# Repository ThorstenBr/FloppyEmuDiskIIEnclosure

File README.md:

# FloppyEmu Disk II Enclosure
This project contains OpenSCAD files, STL files, stickers and KiCad PCB to create a 3D-printed custom enclosure for the [Big Mess of Wires - FloppyEmu](https://www.bigmessowires.com/floppy-emu/) - an SD-card based disk drive emulator for the Apple II computer. The custom enclosure is a look-alike of the historic "Disk II" drive, Apple's first and hugely successful original disk drive for the Apple II, introduced in 1978.

As a bonus, this project also contains a housing for the Floppy Emu DB-19 plug adapter - a separate little 3D-print to protect the adapter (see "Bonus" section below).

## Credits
The idea for this 3D-printing project was triggered by similar ideas to create Disk II-shaped custom enclosures for the FloppyEmu in the [AppleFritter](http://www.applefritter.com) forum - a forum for vintage Apple computer fans. See [this discussion thread](https://www.applefritter.com/content/yet-another-floppyemu-enclosure-3d-printing-approach) for more.

## License
This project is released under the "Creative Commons Attribution 4.0 International Public License". See [LICENSE](/LICENSE).

The Apple logo is a registered trademark of Apple Computer Inc. Any images and photos which may show the Disk II-FloppyEmu enclosure with an Apple logo were only given as an example of how you could decorate your Disk II-FloppyEmu drive enclosure for your personal use, to match the retro look of your wonderful original Apple II computer. The 3D-printed Disk II FloppyEmu enclosure is not endorsed by Apple. This project does not grant you any rights or licenses to distribute any 3D-printed enclosures with an Apple logo.

## Design
The 3D design is done with OpenSCAD. All files are available in the [scad](/scad/) folder.

The OpenSCAD file provides an option to generate the enclosure in different sizes. The minimum scale to fit the FloppyEmu PCB is 0.6 (= 60% of the original Disk II enclosure size). Currently, this reduced size is the only variant which is tested. The photos of the enclosure also show this reduced variant. Larger sizes will still require some tweaking in the SCAD files. The full-sized variant will be supported in the future (wait for it...).
You can also choose whether to use one LED (status LED only), or two LEDs (status + power LED). One LED is the default.

You can also find a ready-to-use STL files in the [stl](/stl/) folder. These STL files apply to the tested variant (60% of the original, one LED).

## Button Panel
You will need a button panel, so you can control FloppyEmu from the front.
You can build the panel manually using a perfboard or order a printed circuit board (from JLCPCB etc).

The [pcb](/pcb/) folder contains all Gerber files required for a PCB order:

Alternatively, use a perfboard to solder the push buttons manually. It's only 4 buttons and a connector (and maybe the resistor for the status LED):

Schematics and the KiCad project for the PCB are also stored in [pcb](/pcb/) folder:

The button PCB is eventually screwed to the front panel (Note: the photo does not show the latest design. The PCB is now mounted with 4 screws, one in each corner - see newer PCB design above).

### Bill Of Materials

Here's what you need.

#### For the button panel:

- Manufactured PCB (i.e. upload the Gerber-Files to a PCB manufacturer, like JLCPCB). Alternatively use a [perfboard](https://en.wikipedia.org/wiki/Perfboard).
- 4x "micro switch push button 6x6x7mm" (ebay etc)
- 1x 3mm LED (red)
- 1x resistor (value depends on the type and intensity of your LED, usually 330 Ohm to 1KOhm)
- "2x5 box header" or, alternatively, "2x5 straight pin header"

The four push buttons are very common and easy to obtain. They are similar as the onboard buttons of FloppyEmu. Except the PCB design is made for a through-hole type push buttons (not SMD buttons as on FloppyEmu). Switches with a 7mm peg are required to properly mount the printed button caps. Check on ebay searching for "micro switch push button 6x6x7mm". Your favourite electronics supplier should also have them (Germany: reichelt.de, TASTER 9303, Kurzhubtaster 6x6mm, 7,0mm).

#### For the button panel and LCD connector:
- You can use simple breadboard wires ("jumper wires") to connect FloppyEmu to the button panel and LCD. They are cheap and also come with a ribbon cable. The LCD and the button panel both require 7 wires each (since 3 pins of the button panel's pin header are unused).

- Alternatively, use "header plugs" with matching ribbon cable (2x5 for the button panel, 2x8 for the LCD) - as shown in the build photos. This is a slightly more expensive and complex solution. 

## Wiring FloppyEmu
The FloppyEmu PCB does not provide convenient pins or solder pads to tap the button and LED status signals. However, it's still relatively easy to tap the required signals - as shown by these photos. The photos apply to the Revision C model of the BMOW FloppyEmu. For other revisions, better verify the wiring with a multimeter.

A single wire is enough for each push button is enough: all four push buttons, including the reset button, connect to common ground. The status LED, however, does not connect to ground: it's wired between the status output signal and +5V (via an appropriate resistor for the LED, of course). The only feasible place is to solder directly next to the LED. The status signal is on the right of the LED – as shown. Be careful when soldering – just touch the LED very briefly with the iron – otherwise the onboard LED will die.

You can wire the ground lead (common for all push buttons) and the 5V (for the status LED) to the unpopulated debug connector in the middle of the FloppyEmu PCB. I soldered these two on the PCB’s bottom side, so they are almost “invisible” once the PCB is installed.

I suggest you solder all wires to a 2x5 pin header (or boxed header), so you can use a neat ribbon cable with plugs to connect the front button panel. The ribbon cable connects all four button signals, the status signal, ground and 5V – so three pins remain unused. If you wanted a power LED – just connect between ground and 5V (via a resistor, of course). See the schematics in the [pcb](/pcb) folder for a suggested pin assignment of the pin header/ribbon cable.

## 3D Print
3D printing is straight forward. The models should be printed with their flat side facing downwards.

Preferably use white or light gray filament for the top shell, base plate, and for the rear panel. Use black filament for the front panel and the buttons.

The models are optimized to reduce 3D "supports", however, the top shell and the front panel still need "supports" to be enabled when printing.

The buttons should be printed without supports. Two brackets are also printed: a bracket for the PCB (feet to tbe attached to the PCB rear). And a bracket for the cable strain-relief (cable can be attached to a mount at the top/rear of the shell).

The large grooves on the top shell do require supports though - since this model should be printed upside down:

Carefully remove the printed "supports" to reveal the top grooves:

### Print Duration
The top shell takes about 7 hours to print on an Ender 3v2.
The front and rear panel require about 1:30 hours.
The buttons and mounting brackets require about 30 minutes.

## Assembly

### Shell
The top shell and the base plate should be glued together. Make sure to completely cover the seam between these two elements, since these two parts were split for easier 3D printing, and the original Disk II does have different seams. Smoothing these seams (before applying beige "Apple II"-like paint - I used spray-paint) comepletely hides the seam. Glueing these two parts also provides extra strength: there should be no more wobble or flexing once the two parts are glued.

### Front Panel
First, the PCB is directly attached to the front panel with two screws.
The rear of the PCB is screwed to the printed mounting bracket ("PCB feet").
Then, attach the button PCB (perfboard of printed circuit board) with four screws to the front panel.
Make sure the four buttons are working fine
The push buttons only travel 0.25mm when depressed.
If the PCB was slightly warped or the buttons are soldered unevenly, slightly adjust the distance between the PCB and the front-panel.
Just unscrewing one of the four screws to release a bit of pressure may already be enough.

The LCD display is clipped into the front panel. The pegs should exactly fit to the original FloppyEmu LCD.
If necessary, use glue to prevent the LCD from slipping from the little pegs (this should normally not be necessary though, if you do not clip and remove the LCD from the front panel too often).

Use a ribbon cable to connect the LCD to the original connector on the FloppyEmu PCB (make sure to connect the cable with the correct orientation!).
Depending on the connector plugs, you may need to slightly bend the pins on the LCD, so they are angled 10-20° downward (may be necessary if the plug is too high and touches the top of the shell).

Eventually, when everything is connected, the whole assembly slides into the front of the 3D-printed shell.

The front panel and the rear-bracket of the PCB are fixed to the base plate with screws from the bottom of the shell.

Once the PCB/front-panel is installed, connect the disk drive ribbon cable and use the printed cable bracket to attach the cable to the cable strain-relief at the top of the shell. This also guides the cable towards the cable slot in the rear-panel (photos above do not quite match: the cable strain-relief has since moved from the rear panel to the top of the shell).

Finally attach the rear panel with two screws from the bottom.

Almost done!

But remember: it's not complete... without rubber feet... :)

Done! :)

## Stickers
By the way, check the [sticker](/sticker/) folder for a collection of stickers to decorate your device.
Several variants of the rear sticker are provided.
The designs are also available as GIMP image files (.xcf), so you can adapt the text to your needs.

The stickers are now also available in high quality [here](/sticker/HighQuality). Many thanks to [khaibitgfx](https://www.applefritter.com/khaibitgfx)!

## Bonus: Floppy Emu DB-19 adapter housing

The Floppy Emu DB-19 adapter is provided as a bare PCB only. It is usually connected to the back of your Apple II and rarely touched. However, you should still be careful with the adapter since the pins carry the +5V rail and also the +/- 12V rails. Since Disk II cable has the +/-12V rails connected to pins which are directly next to disk control and read/write signals (TTL/5V logic). A shortcut between these pins could easily damage the disk controller, the Apple II, or FloppyEmu (or all of them):

The 3D-printed plug adapter housing provides proper protection for the adapter. The adapter PCB slides right into the bottom part of the housing:

The top is printed with some notches, so it snaps right into place - and firmly holds the adapter PCB/plug:

The result is a fairly bulky plug, but that's due to the clunky nature of the "_PCB-box header-header plug-ribbon cable_" assembly.

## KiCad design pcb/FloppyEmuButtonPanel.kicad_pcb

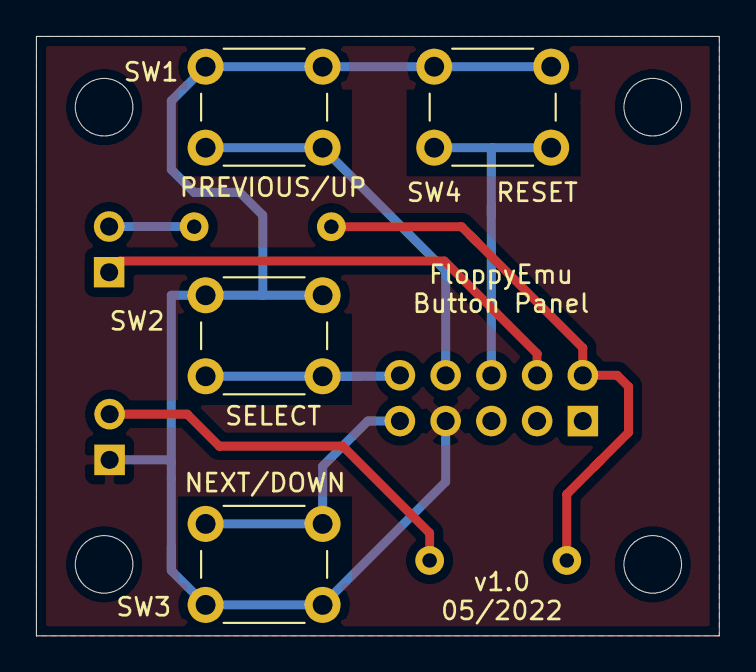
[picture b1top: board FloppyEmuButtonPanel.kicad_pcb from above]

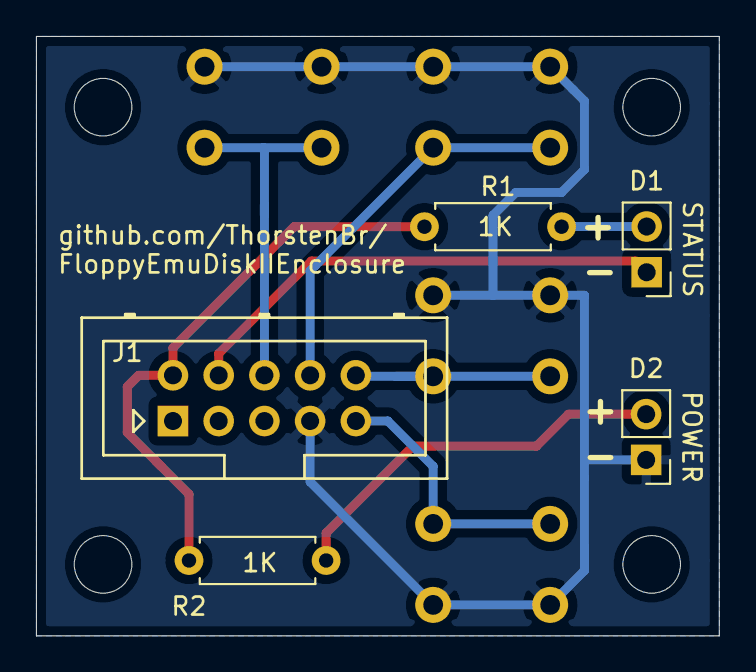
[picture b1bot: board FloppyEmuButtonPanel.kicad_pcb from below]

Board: 2 copper layers, 37.9 x 33.3 mm, 13 parts (5 on the bottom side), 9 nets.

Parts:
D1: STATUS; Pin_Header_Straight_1x02_Pitch2.54mm
D2: POWER; Pin_Header_Straight_1x02_Pitch2.54mm
H1, H2, H3, H4: MountingHole; MountingHole_3.2mm_M3
J1: ButtonPanelConnector; Box_Header_2x05x2.54mm_Straight
R1, R2: 1K; R_Axial_DIN0207_L6.3mm_D2.5mm_P7.62mm_Horizontal
SW1: PREVIOUS/UP; SW_PUSH_6mm_h5mm
SW2: SELECT; SW_PUSH_6mm_h5mm
SW3: NEXT/DOWN; SW_PUSH_6mm_h5mm
SW4: RESET; SW_PUSH_6mm_h5mm

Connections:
+5V: J1.2, R1.1, R2.1
/NEXT: J1.9, SW3.1
/PREVIOUS: J1.8, SW1.2
/RESET: J1.6, SW4.2
/SELECT: J1.10, SW2.2
/STATUS: D1.1, J1.4
GND: D2.1, J1.7, SW1.1, SW2.1, SW3.2, SW4.1
unnamed: D1.2, R1.2
unnamed: D2.2, R2.2

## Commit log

2022-05-15 Added photos.
2022-05-15 Initial version of the main SCAD file.
2022-05-15 Added PCB schematics.
2022-05-16 Added image files and original GIMP xcf files for the front and rear stickers.
2022-05-16 Added KiCad schematics and PCB design for button panel.
2022-05-16 Updated front panel image to match current design.
2022-05-16 Update README.md
    Added push button specification
2022-05-16 Added OpenSCAD files.
2022-05-16 Improved element selection.
2022-05-16 Create LICENSE
2022-05-16 Added license.
2022-05-17 PCB Update
2022-05-17 Corrected button panel (mounting points). Added Gerber files for PCB.
2022-05-17 Added print instructions.
2022-05-17 Moved cable strain-relief from rear panel to top shell which provides much better stability. The strain-relief is angled, so the bracket can still be attached and screwed when the top shell and base 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
2022-05-17 Added STL files for the first version of the small-sized FloppyEmu Disk II enclosure.
2022-05-17 Updated image showing 3D print preview.
2022-05-18 Improved description of required material.
2022-05-18 Prepared support for jumbo display (not tested yet).
2022-05-19 Adapted sticker for Ireland (uses "ltd" instead of "inc", changed to Cork address)
2022-05-22 Added enclosure for Floppy Emu's DB-19 plug adapter.
2022-05-22 Added description of power rails to adapter photo.
2022-06-14 Minor PCB design update.
2023-09-22 Several minor improvements: - Changed "reset button" to a small round button, while the three control buttons keep their larger/rectangular shape. The reset button is barely needed. The round shape a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
2024-09-18 Added sticker for front panel.
2024-10-05 Added highly detailed stickers made by khaibitgfx@applefritter.
